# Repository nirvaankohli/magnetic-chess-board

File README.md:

# Magnetic Chess Board

---

## What is this project?

Magnetic Chess Board is a chessboard with electromagnetic sensors, two key switches, and an OLED display. It tracks each move you make on the board and uploads the game data to a local web server running on your device.

The chessboard itself is powered by a Raspberry Pi Pico W. The board connects wirelessly to your host device and allows you to play physically while having all the benefits of being able to analyze your gameplay later. Games are stored in json & svg format and can also be seen through the web interface on your own device.

---

## Why choose this project?

After creating [MORPH.00](https://github.com/nirvaankohli/MORPH.00/tree/main), a customizable keyboard that changes it's function, I wanted something different. Counsidently my feed showed me a chess board that can move the pieces itself. I orginally wanted to do this because of that video. However, I quickly found out the magic part of moving the pieces autonomously was to expensive. So, I settled for the next best thing, an electromagnetic chess board to analyze and track your moves. It was still such a cool idea because you are turning something physical into something digital. Additionally, let's say your friend comes voer and you play chess, you can expose the endpoint on like a server or something so both of you can look back at the game. Taking all of these things into account, I decided to choose this project. The use of this is legitimate because of the stuff I just mentioned above. 

----

This project is powered by a [Raspberry Pi Pico W](https://www.digikey.com/en/products/detail/raspberry-pi/SC0918/16608263?gclsrc=aw.ds&gad_source=1&gad_campaignid=20243136172&gbraid=0AAAAADrbLljsWjzjlqCOAZTfclDIAHgz4&gclid=Cj0KCQjwrZTRBhDSARIsAHidYfce6rFr-VwDE62IjY7dzyzYrg_4eUx6KZ3DTTBa-lTi34BBF99YXZwaAoAzEALw_wcB) running [MicroPython](https://micropython.org/download/RPI_PICO_W/) with some libraries. This microcontroller is on the top right part of the PCB so the charging port can be exposed and be close to components like the OLED and switches. 

The switches are low profile Choc V1 switches, the OLED a 0.96 Inch 128x64 OLED I2C Display Module, and all the electromagnetic sensors MKA-10110 10X18MM N/O SPST Contact Reed Switches. There is a part of this project on the host computer that hosts the web server that stores all the chess game's states and past move history. 

--- 

## CAD Renderings

My pieces 3D modeling is not the best, ik.

---

## PCB & Schematic

Below, is the PCB w components in multiple views.

Beautiful, right?

---

## Web Page

---

## How it Works

Each square on the board has a reed switch underneath it that detects wether a piece is present. A Raspberry Pi pico W scans all 8 columns and 8 rows of these switches as a key matrix, along with two buttons and an OLED display.

When a piece is moved the Pico W sends the current occupied squares to a local Flask server on the hosts computer(or anywhere). The server compares that physical board state to the saved chess game state(if the game was newly created it spins up a new one) using `python-chess`, finds the legal move that matches, and updates the game history. 

If the move is ambiguous, the OLED shows the possible moves and buttons let the player choose the correct one. After every valid move, the server saves the new board state and updates the web page so the full game can be viewed later.

---

## How To Use

1. Plug in a micro-usb cable into the Pico and the other end into your host computer
2. Install the firmware onto the Pico W(reference [this](code/pico_w/firmware.md) if not sure)
3. Download [the Thonny IDE](https://thonny.org/)
    - Click the bottom-right corner of Thonny and ensure it says MicroPython (Raspberry Pi Pico).
4. Update `code/pico_w/code/secrets.py` with:
    - your Wi-Fi SSID
    - your Wi-Fi password
    - your computer's local server address, like `http://192.168.x.x:5000`
5. In the Thonny Files sidebar, got to the "This computer" section to find the directory `code/pico_w/`. 
6. Right-click all the .py files and select `Upload to` to transfer the files to your pico.
7. Run the host server from `code/host`:
   ```bash
   flask --app app run --debug --host 0.0.0.0
    ```
8. Power on the board and wait for it to connect to WiFi.
9. Hold the white button to start a game(left).
10. Move pieces on the board as usual.
11. The white button confirms the current player's turn.
12. If the board detects multiple possible moves, use the black button to cycle through them and the white button to confirm the correct one.
13. Open the game page in your browser at:
```
http://<your-computer-ip>:5000/game/<game_id>
```
    to view the move history and current board state.

The server saves each game's state in `code/host/game_state/<game_id>.json` and `code/host/game_state/<game_id>.svg`

---

## How to Build/Assemble

Notice: You will need a way to 3D print parts for this & also have to buy all materials from [bom](bom.csv)

1. Go into `hardware/cad/3d-printed/pieces/` and print all the `.stl` files it contains. Below are which ones to print two times. 
    - Print `rook.stl`, `knight.stl`, and `bishop.stl` 2 times each for both black and white.
    - Then print both `queen.stl` and `king.stl` 1 time each for both black and white.
    - Print `disk.stl`s 16 times each for both black & white.
2. For every piece you have printed, put in the N42 magnet in it and put super glue on the remaining space and magnet.
    - Apply superglue to the bottom of a disc that matches the piece’s color, then press it face down into the extra space in the piece’s hole.
3. After you have assembled the pieces, it is time to solder on the components to the PCB board. If you do not know which components match what footprint, please reference `hardware/cad/boards/boards-w-components.step`
4. After doing that you will have to put the top frame(`hardware/cad/3d-printed/top-plate.stl`) onto the board. It should snap in. 
5. Then you will attach the bottom plate(`hardware/cad/3d-printed/bottom-plate.stl`) with a combination of the 4 screw holes(where you will put in the screw and the nut on the other side) and super glue.
6. From there you will need to print out the key caps available in `hardware/cad/3d-printed/key-cap.stl`
6. Now your chess board should be ready to go!

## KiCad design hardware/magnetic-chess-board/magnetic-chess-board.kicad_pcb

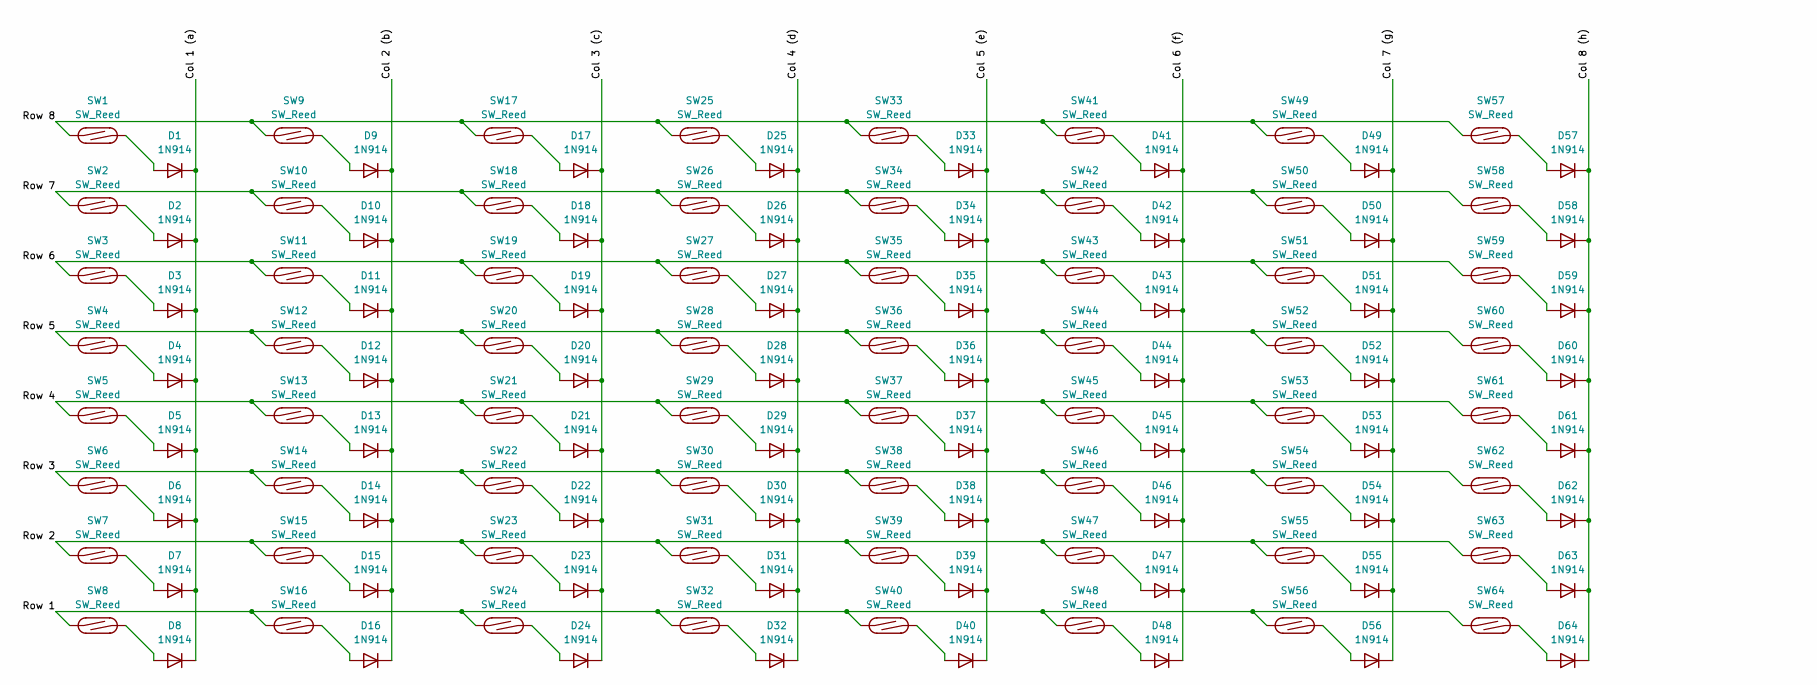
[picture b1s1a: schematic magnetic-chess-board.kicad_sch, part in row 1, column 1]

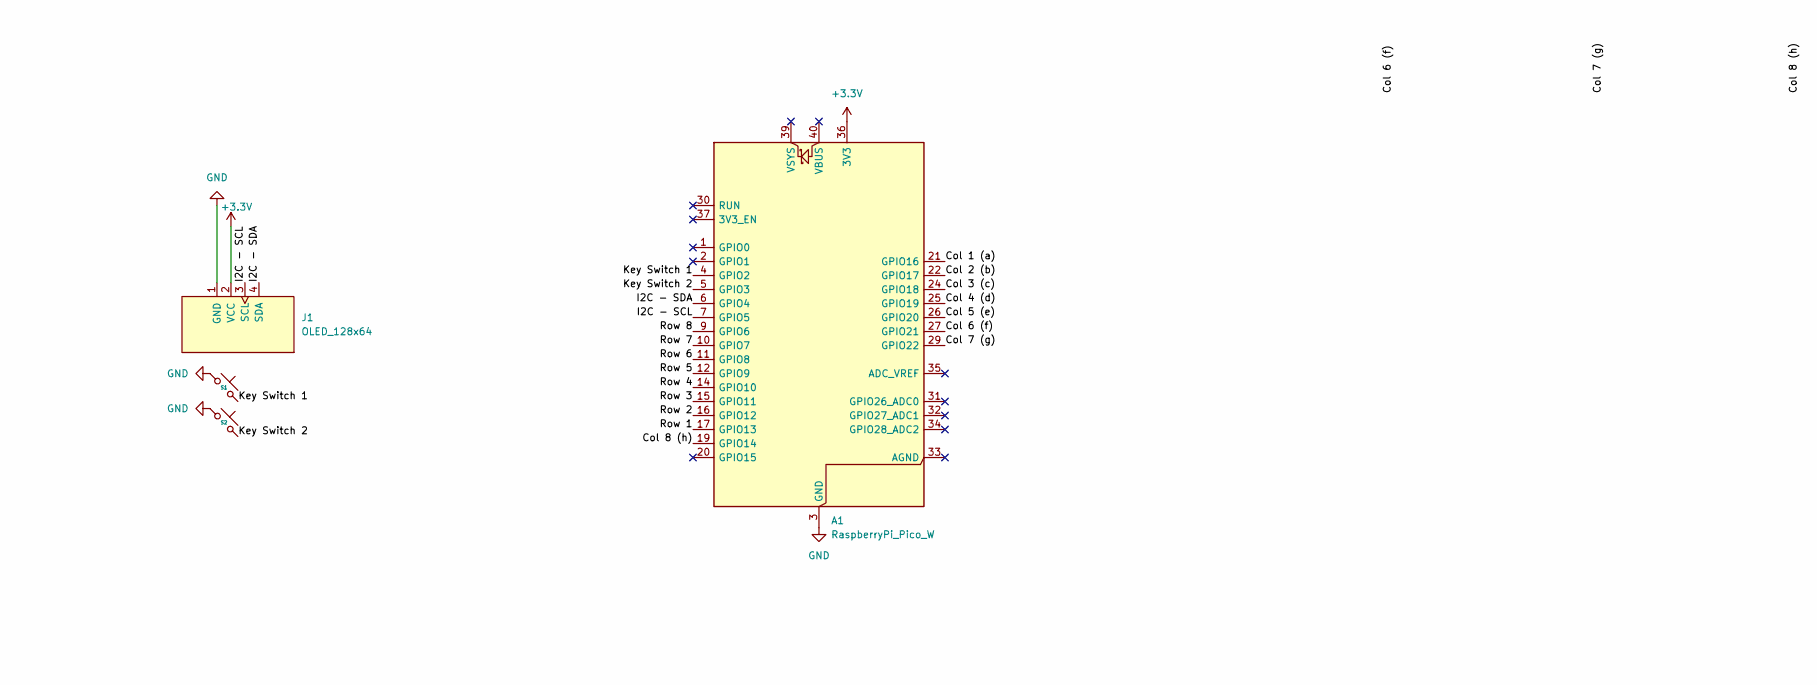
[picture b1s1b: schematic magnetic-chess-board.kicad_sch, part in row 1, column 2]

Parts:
A1: RaspberryPi_Pico_W; RaspberryPi_Pico_W_SMD
D1, D2, D3, D4, D5, D6, D7, D8, D9, D10, D11, D12, D13, D14, D15, D16, D17, D18, D19, D20, D21, D22, D23, D24, D25, D26, D27, D28, D29, D30, D31, D32, D33, D34, D35, D36, D37, D38, D39, D40, D41, D42, D43, D44, D45, D46, D47, D48, D49, D50, D51, D52, D53, D54, D55, D56, D57, D58, D59, D60, D61, D62, D63, D64: 1N914; D_DO-35_SOD27_P7.62mm_Horizontal
J1: OLED_128x64
S1, S2: SW_Hotswap_Kailh_Choc_V1
SW1, SW2, SW3, SW4, SW5, SW6, SW7, SW8, SW9, SW10, SW11, SW12, SW13, SW14, SW15, SW16, SW17, SW18, SW19, SW20, SW21, SW22, SW23, SW24, SW25, SW26, SW27, SW28, SW29, SW30, SW31, SW32, SW33, SW34, SW35, SW36, SW37, SW38, SW39, SW40, SW41, SW42, SW43, SW44, SW45, SW46, SW47, SW48, SW49, SW50, SW51, SW52, SW53, SW54, SW55, SW56, SW57, SW58, SW59, SW60, SW61, SW62, SW63, SW64: SW_Reed; MKA-14103

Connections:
+3.3V: A1.36 (3V3), J1.2 (VCC)
/Col 1 (a): A1.21 (GPIO16), D1.1 (K), D2.1 (K), D3.1 (K), D4.1 (K), D5.1 (K), D6.1 (K), D7.1 (K), D8.1 (K)
/Col 2 (b): A1.22 (GPIO17), D9.1 (K), D10.1 (K), D11.1 (K), D12.1 (K), D13.1 (K), D14.1 (K), D15.1 (K), D16.1 (K)
/Col 3 (c): A1.24 (GPIO18), D17.1 (K), D18.1 (K), D19.1 (K), D20.1 (K), D21.1 (K), D22.1 (K), D23.1 (K), D24.1 (K)
/Col 4 (d): A1.25 (GPIO19), D25.1 (K), D26.1 (K), D27.1 (K), D28.1 (K), D29.1 (K), D30.1 (K), D31.1 (K), D32.1 (K)
/Col 5 (e): A1.26 (GPIO20), D33.1 (K), D34.1 (K), D35.1 (K), D36.1 (K), D37.1 (K), D38.1 (K), D39.1 (K), D40.1 (K)
/Col 6 (f): A1.27 (GPIO21), D41.1 (K), D42.1 (K), D43.1 (K), D44.1 (K), D45.1 (K), D46.1 (K), D47.1 (K), D48.1 (K)
/Col 7 (g): A1.29 (GPIO22), D49.1 (K), D50.1 (K), D51.1 (K), D52.1 (K), D53.1 (K), D54.1 (K), D55.1 (K), D56.1 (K)
/Col 8 (h): A1.19 (GPIO14), D57.1 (K), D58.1 (K), D59.1 (K), D60.1 (K), D61.1 (K), D62.1 (K), D63.1 (K), D64.1 (K)
/I2C - SCL: A1.7 (GPIO5), J1.3 (SCL)
/I2C - SDA: A1.6 (GPIO4), J1.4 (SDA)
/Key Switch 1: A1.4 (GPIO2), S1.2
/Key Switch 2: A1.5 (GPIO3), S2.2
/Row 1: A1.17 (GPIO13), SW8.1, SW16.1, SW24.1, SW32.1, SW40.1, SW48.1, SW56.1, SW64.1
/Row 2: A1.16 (GPIO12), SW7.1, SW15.1, SW23.1, SW31.1, SW39.1, SW47.1, SW55.1, SW63.1
/Row 3: A1.15 (GPIO11), SW6.1, SW14.1, SW22.1, SW30.1, SW38.1, SW46.1, SW54.1, SW62.1
/Row 4: A1.14 (GPIO10), SW5.1, SW13.1, SW21.1, SW29.1, SW37.1, SW45.1, SW53.1, SW61.1
/Row 5: A1.12 (GPIO9), SW4.1, SW12.1, SW20.1, SW28.1, SW36.1, SW44.1, SW52.1, SW60.1
/Row 6: A1.11 (GPIO8), SW3.1, SW11.1, SW19.1, SW27.1, SW35.1, SW43.1, SW51.1, SW59.1
/Row 7: A1.10 (GPIO7), SW2.1, SW10.1, SW18.1, SW26.1, SW34.1, SW42.1, SW50.1, SW58.1
/Row 8: A1.9 (GPIO6), SW1.1, SW9.1, SW17.1, SW25.1, SW33.1, SW41.1, SW49.1, SW57.1
GND: A1.3 (GND), A1.8 (GND), A1.13 (GND), A1.18 (GND), A1.23 (GND), A1.28 (GND), A1.38 (GND), J1.1 (GND), S1.1, S2.1
unnamed: D1.2 (A), SW1.2
unnamed: D2.2 (A), SW2.2
unnamed: D3.2 (A), SW3.2
unnamed: D4.2 (A), SW4.2
unnamed: D5.2 (A), SW5.2
unnamed: D6.2 (A), SW6.2
unnamed: D7.2 (A), SW7.2
unnamed: D8.2 (A), SW8.2
unnamed: D9.2 (A), SW9.2
unnamed: D10.2 (A), SW10.2
unnamed: D11.2 (A), SW11.2
unnamed: D12.2 (A), SW12.2
unnamed: D13.2 (A), SW13.2
unnamed: D14.2 (A), SW14.2
unnamed: D15.2 (A), SW15.2
unnamed: D16.2 (A), SW16.2
unnamed: D17.2 (A), SW17.2
unnamed: D18.2 (A), SW18.2
unnamed: D19.2 (A), SW19.2
unnamed: D20.2 (A), SW20.2
unnamed: D21.2 (A), SW21.2
unnamed: D22.2 (A), SW22.2
unnamed: D23.2 (A), SW23.2
unnamed: D24.2 (A), SW24.2
unnamed: D25.2 (A), SW25.2
unnamed: D26.2 (A), SW26.2
unnamed: D27.2 (A), SW27.2
unnamed: D28.2 (A), SW28.2
unnamed: D29.2 (A), SW29.2
unnamed: D30.2 (A), SW30.2
unnamed: D31.2 (A), SW31.2
unnamed: D32.2 (A), SW32.2
unnamed: D33.2 (A), SW33.2
unnamed: D34.2 (A), SW34.2
unnamed: D35.2 (A), SW35.2
unnamed: D36.2 (A), SW36.2
unnamed: D37.2 (A), SW37.2
unnamed: D38.2 (A), SW38.2
unnamed: D39.2 (A), SW39.2
unnamed: D40.2 (A), SW40.2
unnamed: D41.2 (A), SW41.2
unnamed: D42.2 (A), SW42.2
unnamed: D43.2 (A), SW43.2
unnamed: D44.2 (A), SW44.2
unnamed: D45.2 (A), SW45.2
unnamed: D46.2 (A), SW46.2
unnamed: D47.2 (A), SW47.2
unnamed: D48.2 (A), SW48.2
unnamed: D49.2 (A), SW49.2
unnamed: D50.2 (A), SW50.2
unnamed: D51.2 (A), SW51.2
unnamed: D52.2 (A), SW52.2
unnamed: D53.2 (A), SW53.2
unnamed: D54.2 (A), SW54.2
unnamed: D55.2 (A), SW55.2
unnamed: D56.2 (A), SW56.2
unnamed: D57.2 (A), SW57.2
unnamed: D58.2 (A), SW58.2
unnamed: D59.2 (A), SW59.2
unnamed: D60.2 (A), SW60.2
unnamed: D61.2 (A), SW61.2
unnamed: D62.2 (A), SW62.2
unnamed: D63.2 (A), SW63.2
unnamed: D64.2 (A), SW64.2

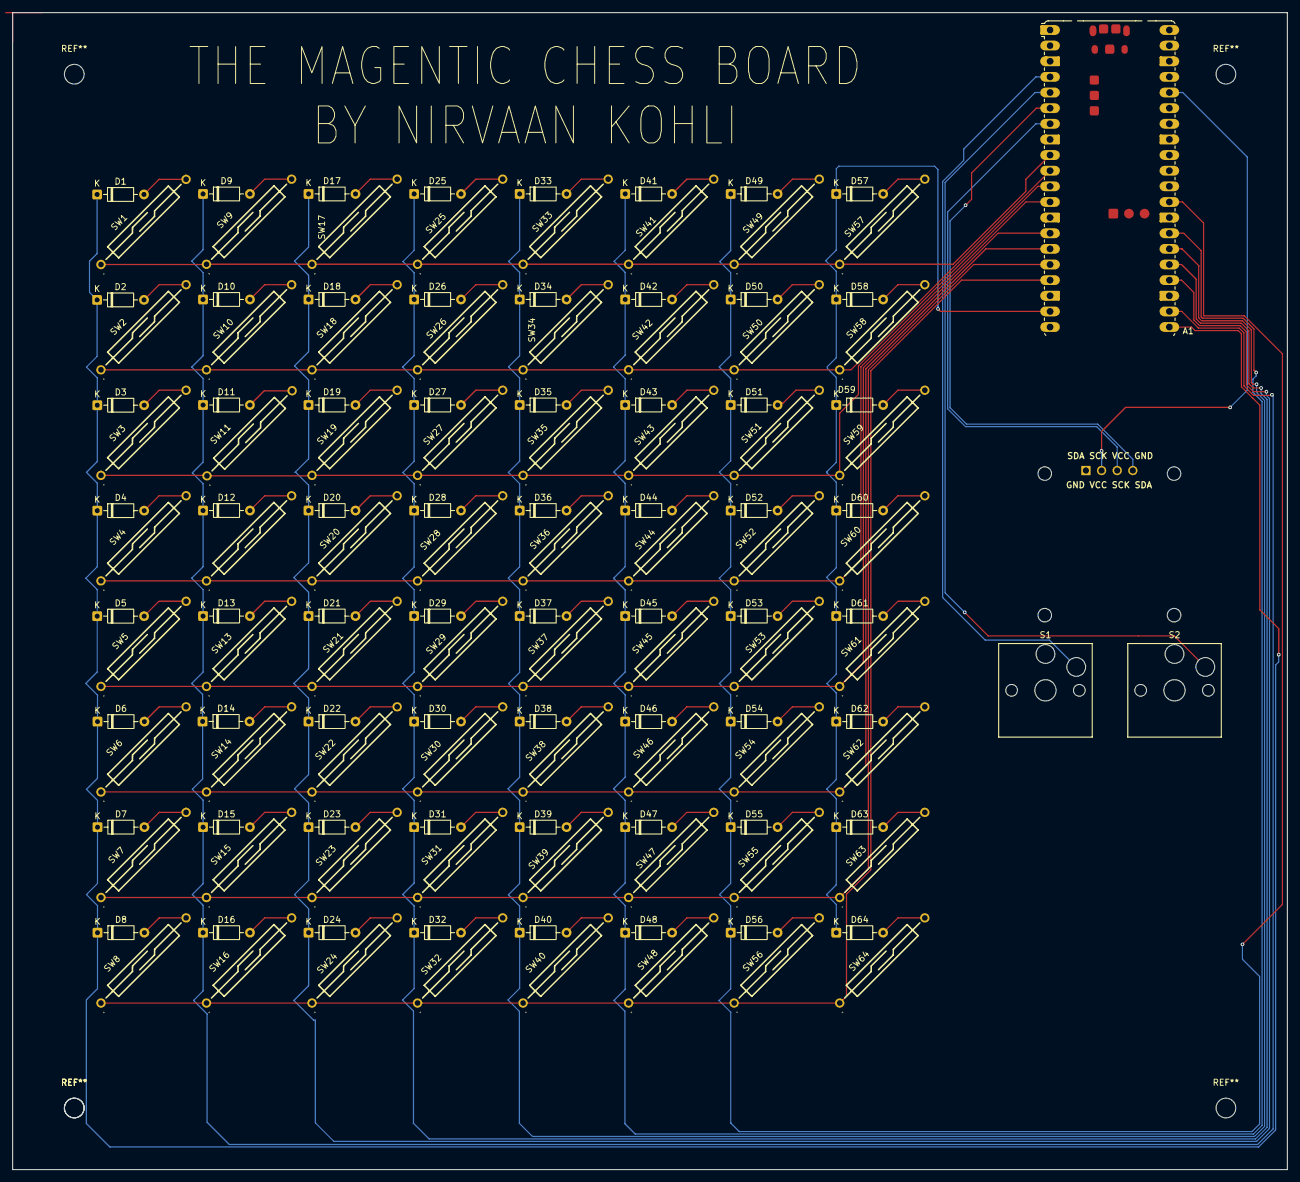
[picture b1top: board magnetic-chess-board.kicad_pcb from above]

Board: 2 copper layers, 207.1 x 188.0 mm, 132 parts (0 on the bottom side), 86 nets.

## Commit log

2026-05-20 Refactor code structure for improved readability and maintainability
2026-05-23 yooo
2026-05-24 Sun May 24 - Fixed handling of 2+ possiblities on move then display on OLED and make them choose which one they want, also fix logic on invalid and ambiogous requests. Added Text on Oled
2026-05-25 On host implement game_id intgration
2026-05-25 more game_id flow from the pico so it works
2026-06-13 final??
2026-06-13 minor folder rename and Readme improvement
2026-06-13 is .history removable?
2026-06-13 reduce redundancy and
2026-06-13 bom update
2026-06-17 Fix some changes
